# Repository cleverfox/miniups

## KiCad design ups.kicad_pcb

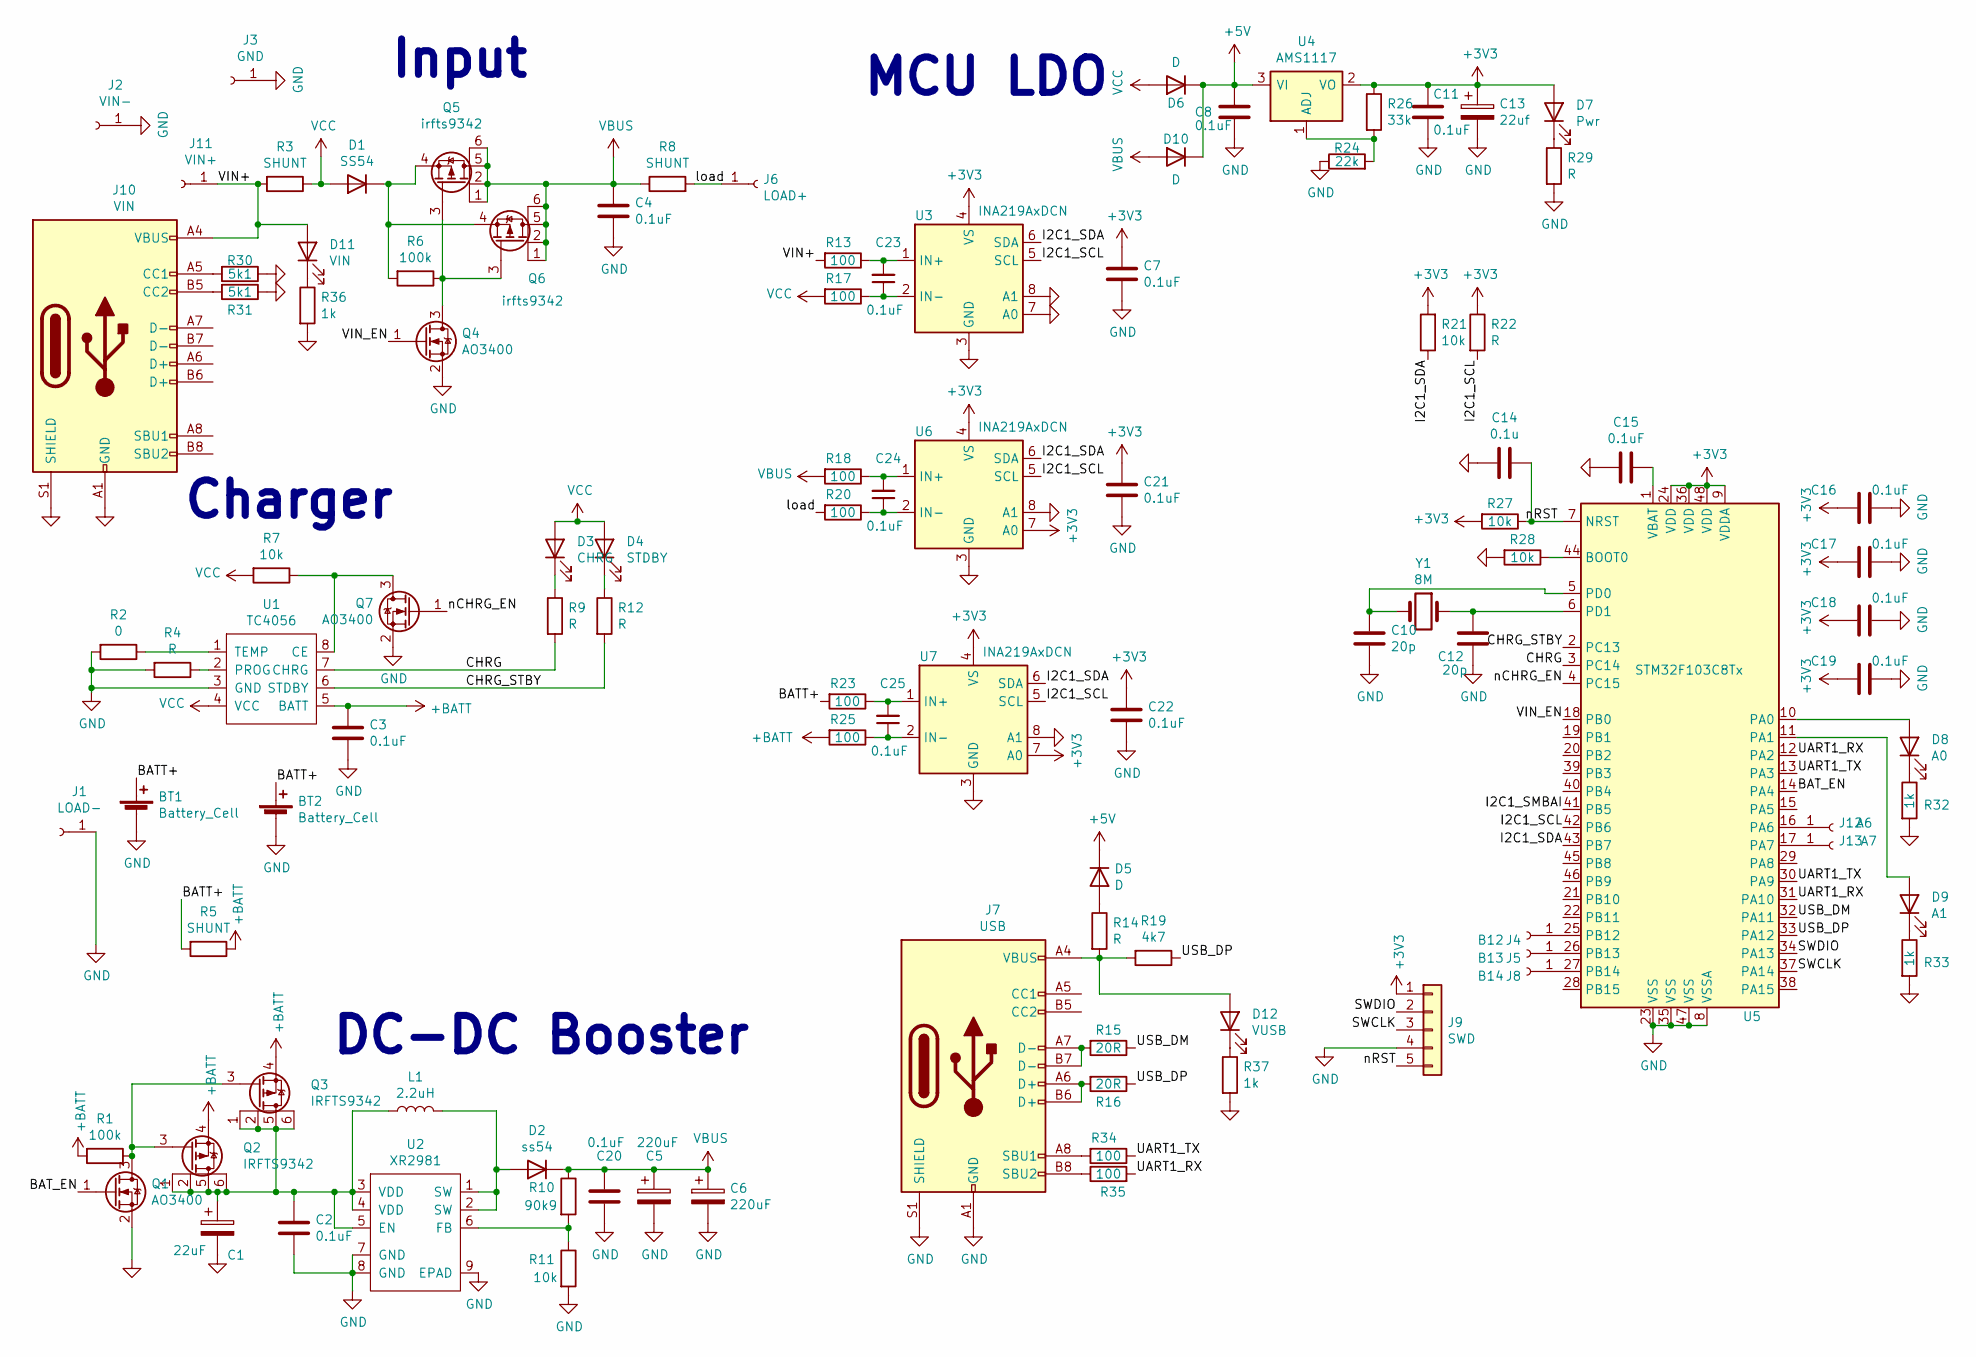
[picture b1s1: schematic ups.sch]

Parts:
BT1, BT2: Battery_Cell; BatteryHolder_MPD_BH-18650-PC2
C1: 22uF; C_Elec_6.3x7.7
C2, C3, C4, C7, C8, C11, C15, C16, C17, C18, C19, C20, C21, C22, C23, C24, C25: 0.1uF; C_0603_1608Metric
C5, C6: 220uF; C_Elec_6.3x7.7
C10, C12: 20p; C_0603_1608Metric
C13: 22uf; C_Elec_3x5.4
C14: 0.1u; C_0603_1608Metric
D1: SS54; D_SMC
D2: ss54; D_SMC
D3: CHRG; LED_0805_2012Metric
D4: STDBY; LED_0805_2012Metric
D5, D6, D10: D; LED_0805_2012Metric
D7: Pwr; LED_0805_2012Metric
D8: A0; LED_0805_2012Metric
D9: A1; LED_0805_2012Metric
D11: VIN; LED_0805_2012Metric
D12: VUSB; LED_0805_2012Metric
J1: LOAD-; conn1_2mm
J2: VIN-; conn1_2mm
J3: GND; conn1_2mm
J4: B12; testpoint
J5: B13; testpoint
J6: LOAD+; conn1_2mm
J7: USB; USB_C_Receptacle_HRO_TYPE-C-31-M-12
J8: B14; testpoint
J9: SWD; PinHeader_1x05_P2.54mm_Vertical
J10: VIN; USB_C_Receptacle_HRO_TYPE-C-31-M-12
J11: VIN+; conn1_2mm
J12: A6; testpoint
J13: A7; testpoint
L1: 2.2uH; L_10.4x10.4_H4.8
Q1, Q4, Q7: AO3400; SOT-23
Q2, Q3: IRFTS9342; SOT-23-6
Q5, Q6: irfts9342; SOT-23-6
R1, R6: 100k; R_0603_1608Metric
R2: 0; R_0603_1608Metric
R3, R5, R8: SHUNT; R_1210_3225Metric
R4, R9, R12, R14, R22, R29: R; R_0603_1608Metric
R7, R11, R21, R27, R28: 10k; R_0603_1608Metric
R10: 90k9; R_0603_1608Metric
R13, R17, R18, R20, R23, R25, R34, R35: 100; R_0603_1608Metric
R15, R16: 20R; R_0603_1608Metric
R19: 4k7; R_0603_1608Metric
R24: 22k; R_0603_1608Metric
R26: 33k; R_0603_1608Metric
R30, R31: 5k1; R_0603_1608Metric
R32, R33, R36, R37: 1k; R_0603_1608Metric
U1: TC4056; SOIC-8_3.9x4.9mm_P1.27mm
U2: XR2981; SOIC-8-1EP_3.9x4.9mm_P1.27mm_EP2.29x3mm_ThermalVias
U3, U6, U7: INA219AxDCN; SOT-23-8
U4: AMS1117; SOT-223-3_TabPin2
U5: STM32F103C8Tx; LQFP-48_7x7mm_P0.5mm
Y1: 8M; Crystal_SMD_3225-4Pin_3.2x2.5mm

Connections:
+3V3: C7.1, C11.1, C13.1, C16.2, C17.2, C18.2, C19.2, C21.1, C22.1, D7.2 (A), J9.1, R21.2, R22.1, R26.1, R27.2, U3.4 (VS), U4.2 (VO), U5.9 (VDDA), U5.24 (VDD), U5.36 (VDD), U5.48 (VDD), U6.4 (VS), U6.7 (A0), U7.4 (VS), U7.7 (A0)
+5V: C8.1, D5.1 (K), D6.1 (K), D10.1 (K), U4.3 (VI)
+BATT: C3.1, Q2.4 (S), Q3.4 (S), R1.2, R5.1, R25.2, U1.5 (BATT)
/BATT+: BT1.1 (+), BT2.1 (+), R5.2, R23.2
/BAT_EN: Q1.1 (G), U5.14 (PA4)
/CHRG: R9.2, U1.7 (CHRG), U5.3 (PC14)
/CHRG_STBY: R12.2, U1.6 (STDBY), U5.2 (PC13)
/I2C1_SCL: R22.2, U3.5 (SCL), U5.42 (PB6), U6.5 (SCL), U7.5 (SCL)
/I2C1_SDA: R21.1, U3.6 (SDA), U5.43 (PB7), U6.6 (SDA), U7.6 (SDA)
/I2C1_SMBAI: U5.41 (PB5)
/SWCLK: J9.3, U5.37 (PA14)
/SWDIO: J9.2, U5.34 (PA13)
/UART1_RX: R35.2, U5.12 (PA2), U5.31 (PA10)
/UART1_TX: R34.1, U5.13 (PA3), U5.30 (PA9)
/USB_DM: R15.1, U5.32 (PA11)
/USB_DP: R16.1, R19.1, U5.33 (PA12)
/VIN+: D11.2 (A), J10.A4 (VBUS), J10.A9 (VBUS), J10.B4 (VBUS), J10.B9 (VBUS), J11.1, R3.2, R13.2
/VIN_EN: Q4.1 (G), U5.18 (PB0)
/load: J6.1, R8.2, R20.2
/nCHRG_EN: Q7.1 (G), U5.4 (PC15)
/nRST: C14.1, J9.5, R27.1, U5.7 (NRST)
GND: BT1.2 (-), BT2.2 (-), C1.2, C2.2, C3.2, C4.2, C5.2, C6.2, C7.2, C8.2, C10.1, C11.2, C12.1, C13.2, C14.2, C15.2, C16.1, C17.1, C18.1, C19.1, C20.2, C21.2, C22.2, J1.1, J2.1, J3.1, J7.A1 (GND), J7.A12 (GND), J7.B1 (GND), J7.B12 (GND), J7.S1 (SHIELD), J9.4, J10.A1 (GND), J10.A12 (GND), J10.B1 (GND), J10.B12 (GND), J10.S1 (SHIELD), Q1.2 (S), Q4.2 (S), Q7.2 (S), R2.2, R4.2, R11.2, R24.1, R28.2, R29.2, R30.1, R31.1, R32.2, R33.2, R36.2, R37.2, U1.3 (GND), U2.7 (GND), U2.8 (GND), U2.9 (EPAD), U3.3 (GND), U3.7 (A0), U3.8 (A1), U5.8 (VSSA), U5.23 (VSS), U5.35 (VSS), U5.47 (VSS), U6.3 (GND), U6.8 (A1), U7.3 (GND), U7.8 (A1)
unnamed: C1.1, C2.1, L1.1, Q2.1 (D), Q2.2 (D), Q2.5 (D), Q2.6 (D), Q3.1 (D), Q3.2 (D), Q3.5 (D), Q3.6 (D), U2.3 (VDD), U2.4 (VDD), U2.5 (EN)
unnamed: C10.2, U5.5 (PD0), Y1.2
unnamed: C12.2, U5.6 (PD1), Y1.1
unnamed: C15.1, U5.1 (VBAT)
unnamed: C23.1, R17.1, U3.2 (IN-)
unnamed: C23.2, R13.1, U3.1 (IN+)
unnamed: C24.1, R20.1, U6.2 (IN-)
unnamed: C24.2, R18.1, U6.1 (IN+)
unnamed: C25.1, R25.1, U7.2 (IN-)
unnamed: C25.2, R23.1, U7.1 (IN+)
unnamed: D1.1 (K), Q5.4 (S), Q6.4 (S), R6.2
unnamed: D2.2 (A), L1.2, U2.1 (SW), U2.2 (SW)
unnamed: D3.1 (K), R9.1
unnamed: D4.1 (K), R12.1
unnamed: D5.2 (A), R14.1
unnamed: D7.1 (K), R29.1
unnamed: D8.1 (K), R32.1
unnamed: D8.2 (A), U5.10 (PA0)
unnamed: D9.1 (K), R33.1
unnamed: D9.2 (A), U5.11 (PA1)
unnamed: D11.1 (K), R36.1
unnamed: D12.1 (K), R37.1
unnamed: D12.2 (A), J7.A4 (VBUS), J7.A9 (VBUS), J7.B4 (VBUS), J7.B9 (VBUS), R14.2, R19.2
unnamed: J4.1, U5.25 (PB12)
unnamed: J5.1, U5.26 (PB13)
unnamed: J7.A6 (D+), J7.B6 (D+), R16.2
unnamed: J7.A7 (D-), J7.B7 (D-), R15.2
unnamed: J7.A8 (SBU1), R34.2
unnamed: J7.B8 (SBU2), R35.1
unnamed: J8.1, U5.27 (PB14)
unnamed: J10.A5 (CC1), R30.2
unnamed: J10.B5 (CC2), R31.2
unnamed: J12.1, U5.16 (PA6)
unnamed: J13.1, U5.17 (PA7)
unnamed: Q1.3 (D), Q2.3 (G), Q3.3 (G), R1.1
unnamed: Q4.3 (D), Q5.3 (G), Q6.3 (G), R6.1
unnamed: Q7.3 (D), R7.1, U1.8 (CE)
unnamed: R2.1, U1.1 (TEMP)
unnamed: R4.1, U1.2 (PROG)
unnamed: R10.2, R11.1, U2.6 (FB)
unnamed: R24.2, R26.2, U4.1 (ADJ)
unnamed: R28.1, U5.44 (BOOT0)
VBUS: C4.1, C5.1, C6.1, C20.1, D2.1 (K), D10.2 (A), Q5.1 (D), Q5.2 (D), Q5.5 (D), Q5.6 (D), Q6.1 (D), Q6.2 (D), Q6.5 (D), Q6.6 (D), R8.1, R10.1, R18.2
VCC: D1.2 (A), D3.2 (A), D4.2 (A), D6.2 (A), R3.1, R7.2, R17.2, U1.4 (VCC)

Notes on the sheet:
Input
MCU LDO
Charger
DC-DC Booster

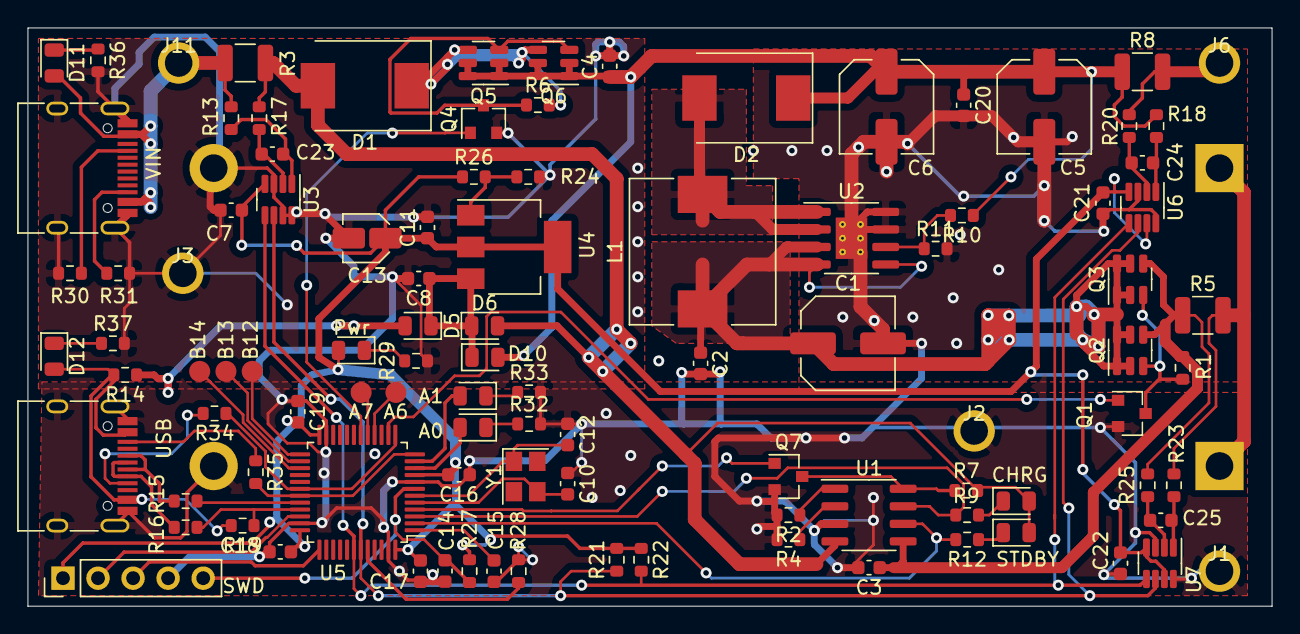
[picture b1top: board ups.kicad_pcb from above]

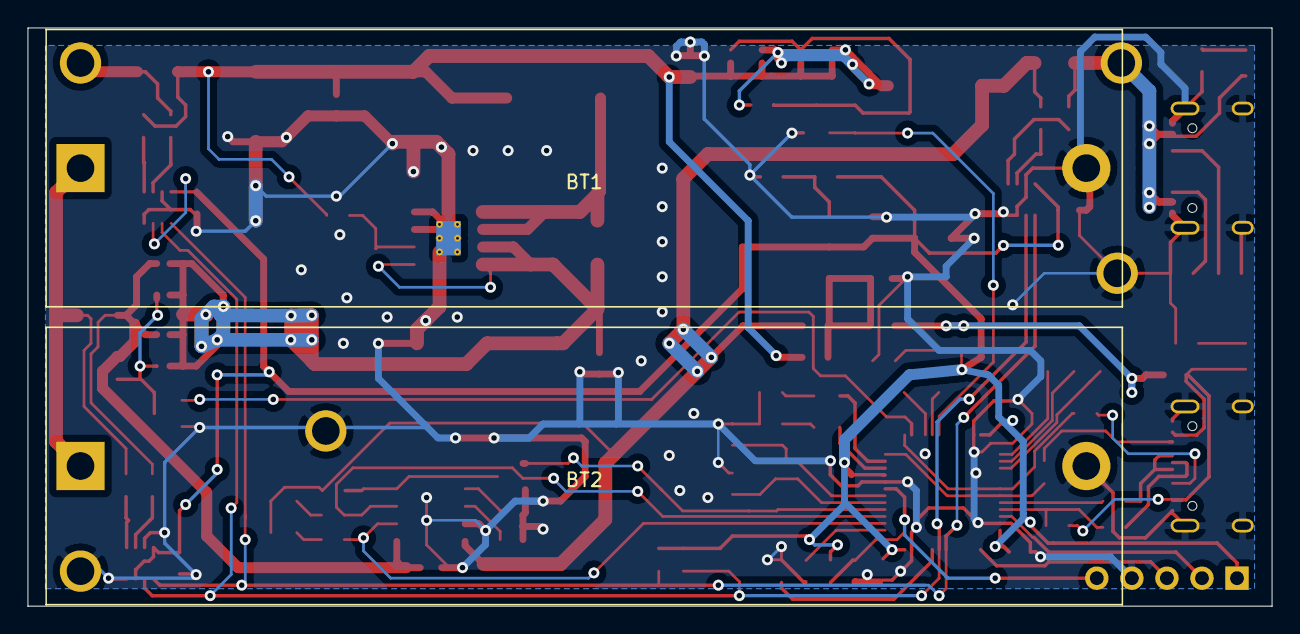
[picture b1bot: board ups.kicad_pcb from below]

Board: 2 copper layers, 90.2 x 41.9 mm, 104 parts (2 on the bottom side), 65 nets.
